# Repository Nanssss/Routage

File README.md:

3IMACS-C Projet Routage

Rey Nans
Raucroy Audrey
Behro Christine

<<<<<<< HEAD
Placement terminé, prise en compte de vos conseils.
Nous avons mis les librairies .lib et .pretty du relai dans le dossier TR_Lib_Ampli.

Attente du go/nogo
=======
Routage effectué en double face.
>>>>>>> routage5

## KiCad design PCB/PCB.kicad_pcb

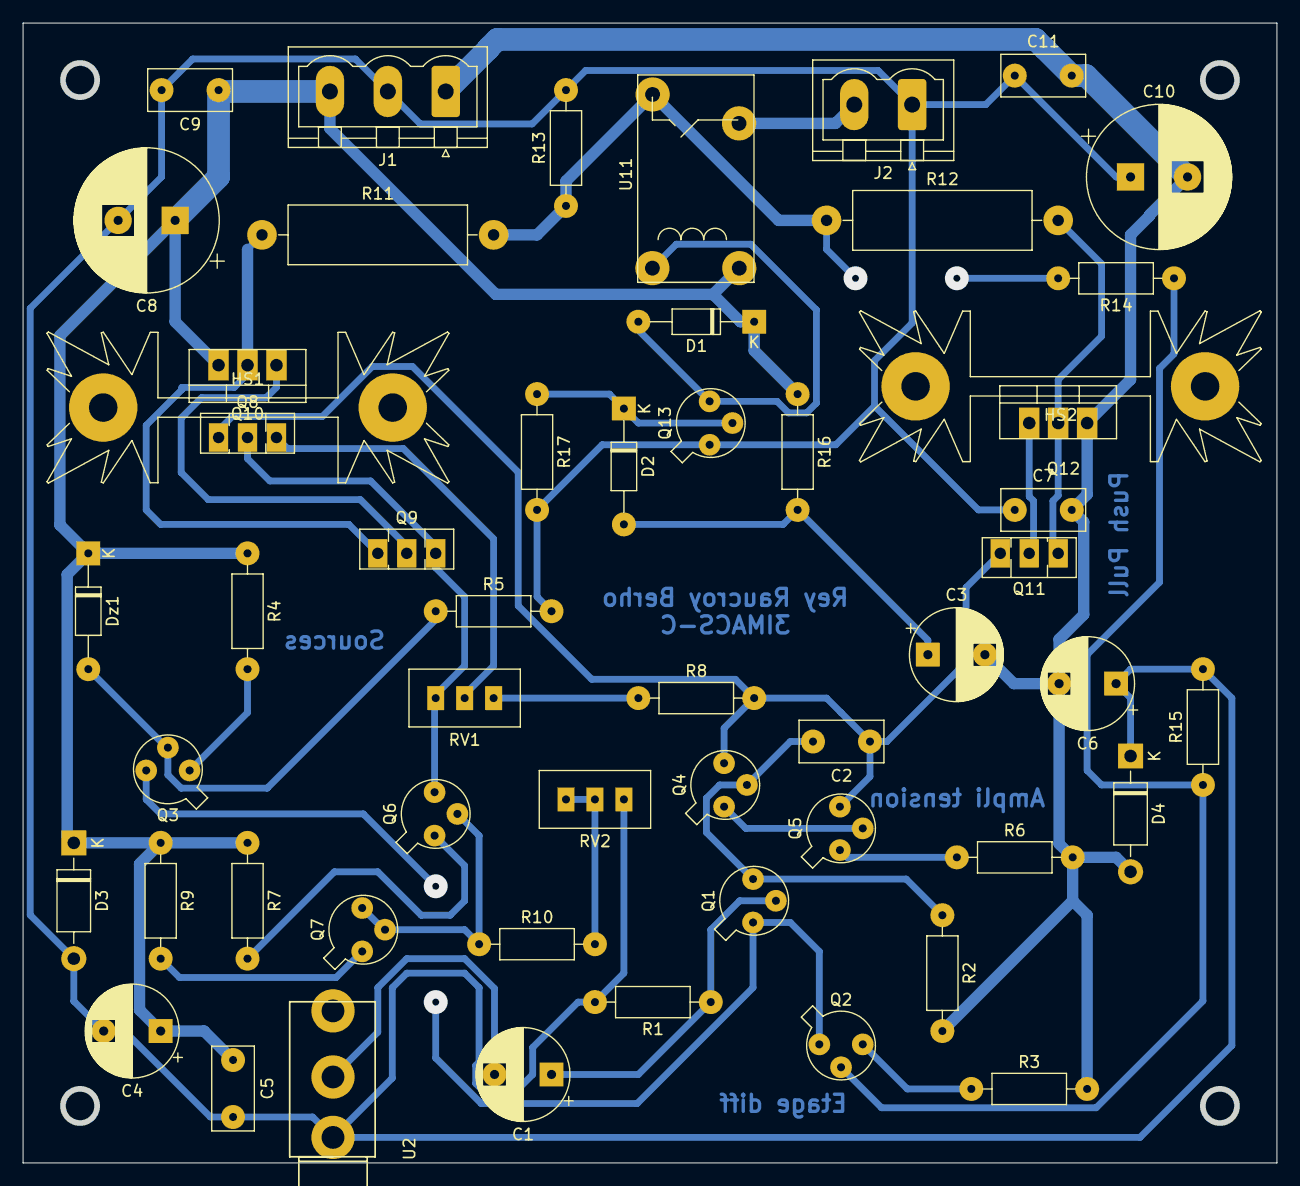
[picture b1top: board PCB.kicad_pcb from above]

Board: 2 copper layers, 110.0 x 100.0 mm, 54 parts (0 on the bottom side), 30 nets.

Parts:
C1, C3: 47u; CP_Radial_D8.0mm_P5.00mm
C2: C; C_Rect_L7.2mm_W3.5mm_P5.00mm_FKS2_FKP2_MKS2_MKP2
C4, C6: 10u; CP_Radial_D8.0mm_P5.00mm
C5, C7, C9, C11: 100n; C_Rect_L7.2mm_W3.5mm_P5.00mm_FKS2_FKP2_MKS2_MKP2
C8, C10: 470u; CP_Radial_D12.5mm_P5.00mm
D1, D2: 1N4148; D_DO-35_SOD27_P10.16mm_Horizontal
D3, D4: 1N4001; D_DO-41_SOD81_P10.16mm_Horizontal
Dz1: BZX55C5V1; D_DO-35_SOD27_P10.16mm_Horizontal
HS1, HS2: Heatsink; Heatsink_Fischer_SK104-STC-STIC_35x13mm_2xDrill2.5mm
J1: Conn_01x03; PhoenixContact_MSTBVA_2,5_3-G-5,08_1x03_P5.08mm_Vertical
J2: Conn_01x02; PhoenixContact_MSTBVA_2,5_2-G-5,08_1x02_P5.08mm_Vertical
Q1, Q2, Q3, Q6, Q7: 2N2907; TO-18-3
Q4, Q5, Q13: 2N2222; TO-18-3
Q8, Q9: BD139; TO-126-3_Vertical
Q10: TIP32; TO-220-3_Vertical
Q11: BD138; TO-126-3_Vertical
Q12: TIP31; TO-220-3_Vertical
R1, R2, R3, R4, R5, R6, R7, R8, R9, R10, R13, R14, R15, R16, R17: R; R_Axial_DIN0207_L6.3mm_D2.5mm_P10.16mm_Horizontal
R11, R12: R; R_Axial_DIN0516_L15.5mm_D5.0mm_P20.32mm_Horizontal
RV1, RV2: R_POT; Potentiometer_Bourns_3296W_Vertical
U2: Jack_Mono; Jack_35RAPC2AV
U11: Relai

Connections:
+12V: C4.1, C5.1, C8.1, C9.1, D1.1, D3.1, Dz1.1, J1.3, Q10.3, R4.1, R7.1, R9.1, R16.1, U11.b2
-12V: C3.2, C6.2, C7.2, C10.2, C11.2, D4.2, J1.1, Q12.3, R2.2, R3.2, R6.2
GND: C4.2, C5.2, C6.1, C7.1, C8.2, C9.2, C10.1, C11.1, D3.2, D4.1, J1.2, J2.1, Q13.1, R1.2, R5.2, R13.2, R15.2, R17.2, RV2.3, U2.G
unnamed: C1.1, Q1.2, R1.1
unnamed: C1.2, U2.T
unnamed: C2.1, Q4.3, Q5.3, Q8.1, Q11.3, R8.2
unnamed: C2.2, Q1.3, Q4.2, R2.1
unnamed: C3.1, D2.2, R16.2
unnamed: D1.2, Q13.3, U11.b1
unnamed: D2.1, Q13.2, R17.1
unnamed: Dz1.2, Q3.2, R5.1
unnamed: J2.2, U11.c2
unnamed: Q1.1, Q2.1, Q3.3
unnamed: Q2.2, R14.1, R15.1
unnamed: Q2.3, R3.1
unnamed: Q3.1, R4.2
unnamed: Q4.1, Q5.2
unnamed: Q5.1, R6.1
unnamed: Q6.1, R7.2
unnamed: Q6.2, Q7.2, Q7.3, R10.1
unnamed: Q6.3, Q8.2, Q9.3, RV1.1
unnamed: Q7.1, R9.2
unnamed: Q8.3, RV1.2
unnamed: Q9.2, Q10.1
unnamed: Q9.1, Q10.2, R11.1
unnamed: Q11.1, Q12.2, R12.2
unnamed: Q11.2, Q12.1
unnamed: R8.1, RV1.3
unnamed: R10.2, RV2.1, RV2.2
unnamed: R11.2, R12.1, R13.1, R14.2, U11.c1

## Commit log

2021-03-20 Added * file
2021-03-20 Added . file
2021-03-22 ajout de test1 pour test les branches
2021-03-22 remove de la branch
2021-03-23 Schema presque terminé
2021-03-24 placement quasi fini
2021-03-25 schema termine sauf relai
2021-03-28 schema fini
2021-03-28 tout debut empreinte
2021-03-29 Empreinte terminée, demander vérifs
2021-03-29 Empreinte terminée, demander vérif, Readme à jour
2021-04-01 on passe au routage
2021-04-01 debut routage
2021-04-04 tout est placé mais il faut réorganiser
2021-04-04 tout a été placé mais il faut réorganiser
2021-04-04 Placmement terminé, demande de go/nogo
2021-04-04 Placement terminé, demande de go/nogo
2021-04-04 C10 corrigé
2021-04-05 C8 corrigé
2021-04-05 routage refait en respectant vos conseils
2021-04-05 routage terminé en essayant de tenir compte de vos conseils
2021-04-05 placement terminé
2021-04-05 Placement terminé et ajout de nos lib
2021-04-05 Readme modifié
2021-04-06 placement ok !
2021-04-11 1er routage pas top
2021-04-11 routage debut mieux
2021-04-11 routage j'espère que c'est ok
2021-04-11 vias ajoutés
2021-04-12 routage double face
2021-04-13 new placement
2021-04-13 ca avance un peu
2021-04-13 placement rereterminé
2021-04-13 nulnulnul
2021-04-15 routage terminé
2021-04-15 Routage terminé avec plan de masse
2021-04-16 Routage terminé avec texte
2021-04-16 Routage OK
